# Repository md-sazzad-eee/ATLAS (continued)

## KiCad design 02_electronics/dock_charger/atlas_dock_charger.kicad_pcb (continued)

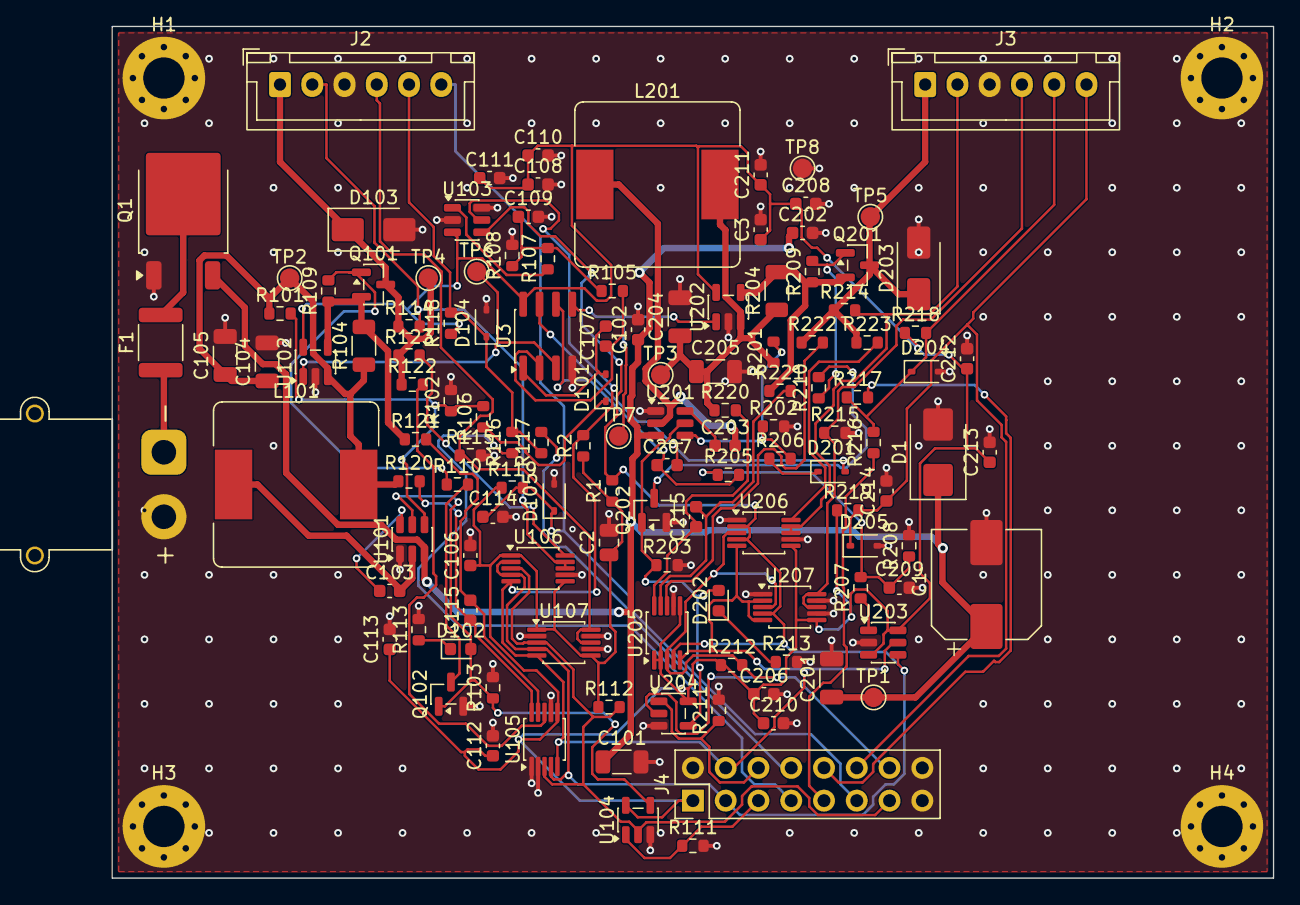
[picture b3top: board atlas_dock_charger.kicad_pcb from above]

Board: 2 copper layers, 90.0 x 66.0 mm, 131 parts (0 on the bottom side), 63 nets.

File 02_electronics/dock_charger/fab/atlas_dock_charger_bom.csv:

"Refs","Value","Footprint","Qty","DNP"
"C1","100uF 25V","Capacitor_SMD:CP_Elec_8x10","1",""
"C2","10uF","Capacitor_SMD:C_0805_2012Metric","1",""
"C3","100nF","Capacitor_SMD:C_0603_1608Metric","1",""
"C101","10uF 25V","Capacitor_SMD:C_1206_3216Metric","1",""
"C102","100nF","Capacitor_SMD:C_0603_1608Metric","1",""
"C103","100nF","Capacitor_SMD:C_0603_1608Metric","1",""
"C104","22uF 25V","Capacitor_SMD:C_1206_3216Metric","1",""
"C105","22uF 25V","Capacitor_SMD:C_1206_3216Metric","1",""
"C106","100nF","Capacitor_SMD:C_0603_1608Metric","1",""
"C107","100nF","Capacitor_SMD:C_0603_1608Metric","1",""
"C108","100nF","Capacitor_SMD:C_0603_1608Metric","1",""
"C109","1uF","Capacitor_SMD:C_0603_1608Metric","1",""
"C110","100nF","Capacitor_SMD:C_0603_1608Metric","1",""
"C111","100nF","Capacitor_SMD:C_0603_1608Metric","1",""
"C112","100nF","Capacitor_SMD:C_0603_1608Metric","1",""
"C113","100nF","Capacitor_SMD:C_0603_1608Metric","1",""
"C114","100nF","Capacitor_SMD:C_0603_1608Metric","1",""
"C115","100nF","Capacitor_SMD:C_0603_1608Metric","1",""
"C201","10uF 25V","Capacitor_SMD:C_1206_3216Metric","1",""
"C202","100nF","Capacitor_SMD:C_0603_1608Metric","1",""
"C203","100nF","Capacitor_SMD:C_0603_1608Metric","1",""
"C204","22uF 25V","Capacitor_SMD:C_1206_3216Metric","1",""
"C205","22uF 25V","Capacitor_SMD:C_1206_3216Metric","1",""
"C206","100nF","Capacitor_SMD:C_0603_1608Metric","1",""
"C207","100nF","Capacitor_SMD:C_0603_1608Metric","1",""
"C208","100nF","Capacitor_SMD:C_0603_1608Metric","1",""
"C209","1uF","Capacitor_SMD:C_0603_1608Metric","1",""
"C210","100nF","Capacitor_SMD:C_0603_1608Metric","1",""
"C211","100nF","Capacitor_SMD:C_0603_1608Metric","1",""
"C212","100nF","Capacitor_SMD:C_0603_1608Metric","1",""
"C213","100nF","Capacitor_SMD:C_0603_1608Metric","1",""
"C214","100nF","Capacitor_SMD:C_0603_1608Metric","1",""
"C215","100nF","Capacitor_SMD:C_0603_1608Metric","1",""
"D1","SMBJ16CA","Diode_SMD:D_SMB","1",""
"D101","BAT54J","Diode_SMD:D_SOD-323","1",""
"D102","AMBER charging","LED_SMD:LED_0603_1608Metric","1",""
"D103","SMAJ12CA","Diode_SMD:D_SMA","1",""
"D104","PESD5V0S1BL","Diode_SMD:D_SOD-323","1",""
"D105","PESD5V0S1BL","Diode_SMD:D_SOD-323","1",""
"D201","BAT54J","Diode_SMD:D_SOD-323","1",""
"D202","AMBER charging","LED_SMD:LED_0603_1608Metric","1",""
"D203","SMAJ12CA","Diode_SMD:D_SMA","1",""
"D204","PESD5V0S1BL","Diode_SMD:D_SOD-323","1",""
"D205","PESD5V0S1BL","Diode_SMD:D_SOD-323","1",""
"F1","3A hold PTC","Fuse:Fuse_1812_4532Metric","1",""
"J1","VIN 4S (+,-)","Connector_AMASS:AMASS_XT30PW-M_1x02_P2.50mm_Horizontal","1",""
"J2","BAY 1 DOCK (VF,VS,GF,GS,DATA,ID)","Connector_JST:JST_XH_B6B-XH-A_1x06_P2.50mm_Vertical","1",""
"J3","BAY 2 DOCK (VF,VS,GF,GS,DATA,ID)","Connector_JST:JST_XH_B6B-XH-A_1x06_P2.50mm_Vertical","1",""
"J4","TO BOARD A","Connector_PinHeader_2.54mm:PinHeader_2x08_P2.54mm_Vertical","1",""
"L101","22uH 2.5A","Inductor_SMD:L_Bourns_SRR1260","1",""
"L201","22uH 2.5A","Inductor_SMD:L_Bourns_SRR1260","1",""
"Q1","AOD409 (rev-pol)","Package_TO_SOT_SMD:TO-252-2","1",""
"Q101","AO3401A","Package_TO_SOT_SMD:SOT-23","1",""
"Q102","2N7002","Package_TO_SOT_SMD:SOT-23","1",""
"Q201","AO3401A","Package_TO_SOT_SMD:SOT-23","1",""
"Q202","2N7002","Package_TO_SOT_SMD:SOT-23","1",""
"R1","2.2k","Resistor_SMD:R_0603_1608Metric","1",""
"R2","2.2k","Resistor_SMD:R_0603_1608Metric","1",""
"R101","130k 0.1%","Resistor_SMD:R_0603_1608Metric","1",""
"R102","10.0k 0.1%","Resistor_SMD:R_0603_1608Metric","1",""
"R103","100k","Resistor_SMD:R_0603_1608Metric","1",""
"R104","20m 1%","Resistor_SMD:R_1206_3216Metric","1",""
"R105","10k","Resistor_SMD:R_0603_1608Metric","1",""
"R106","10k","Resistor_SMD:R_0603_1608Metric","1",""
"R107","10k","Resistor_SMD:R_0603_1608Metric","1",""
"R108","10k","Resistor_SMD:R_0603_1608Metric","1",""
"R109","100k","Resistor_SMD:R_0603_1608Metric","1",""
"R110","10k","Resistor_SMD:R_0603_1608Metric","1",""
"R111","100k","Resistor_SMD:R_0603_1608Metric","1",""
"R112","10k","Resistor_SMD:R_0603_1608Metric","1",""
"R113","1k","Resistor_SMD:R_0603_1608Metric","1",""
"R114","100k","Resistor_SMD:R_0603_1608Metric","1",""
"R115","100k","Resistor_SMD:R_0603_1608Metric","1",""
"R116","1k","Resistor_SMD:R_0603_1608Metric","1",""
"R117","1k","Resistor_SMD:R_0603_1608Metric","1",""
"R118","10k","Resistor_SMD:R_0603_1608Metric","1",""
"R119","10k","Resistor_SMD:R_0603_1608Metric","1",""
"R120","10R","Resistor_SMD:R_0603_1608Metric","1",""
"R121","10R","Resistor_SMD:R_0603_1608Metric","1",""
"R122","10R","Resistor_SMD:R_0603_1608Metric","1",""
"R123","10R","Resistor_SMD:R_0603_1608Metric","1",""
"R201","130k 0.1%","Resistor_SMD:R_0603_1608Metric","1",""
"R202","10.0k 0.1%","Resistor_SMD:R_0603_1608Metric","1",""
"R203","100k","Resistor_SMD:R_0603_1608Metric","1",""
"R204","20m 1%","Resistor_SMD:R_1206_3216Metric","1",""
"R205","10k","Resistor_SMD:R_0603_1608Metric","1",""
"R206","10k","Resistor_SMD:R_0603_1608Metric","1",""
"R207","10k","Resistor_SMD:R_0603_1608Metric","1",""
"R208","10k","Resistor_SMD:R_0603_1608Metric","1",""
"R209","100k","Resistor_SMD:R_0603_1608Metric","1",""
"R210","10k","Resistor_SMD:R_0603_1608Metric","1",""
"R211","100k","Resistor_SMD:R_0603_1608Metric","1",""
"R212","10k","Resistor_SMD:R_0603_1608Metric","1",""
"R213","1k","Resistor_SMD:R_0603_1608Metric","1",""
"R214","100k","Resistor_SMD:R_0603_1608Metric","1",""
"R215","100k","Resistor_SMD:R_0603_1608Metric","1",""
"R216","1k","Resistor_SMD:R_0603_1608Metric","1",""
"R217","1k","Resistor_SMD:R_0603_1608Metric","1",""
"R218","10k","Resistor_SMD:R_0603_1608Metric","1",""
"R219","10k","Resistor_SMD:R_0603_1608Metric","1",""
"R220","10R","Resistor_SMD:R_0603_1608Metric","1",""
"R221","10R","Resistor_SMD:R_0603_1608Metric","1",""
"R222","10R","Resistor_SMD:R_0603_1608Metric","1",""
"R223","10R","Resistor_SMD:R_0603_1608Metric","1",""
"U3","LMV358","Package_SO:SOIC-8_3.9x4.9mm_P1.27mm","1",""
"U101","TPS54202DDC","Package_TO_SOT_SMD:SOT-23-6","1",""
"U102","INA180A2","Package_TO_SOT_SMD:SOT-23-5","1",""
"U103","MCP4725A0T-E/CH","Package_TO_SOT_SMD:SOT-23-6","1",""
"U104","74LVC1G08","Package_TO_SOT_SMD:SOT-23-5","1",""
"U105","INA226 (I, V)","Package_SO:MSOP-10_3x3mm_P0.5mm","1",""
"U106","INA226 (VCHG contact)","Package_SO:MSOP-10_3x3mm_P0.5mm","1",""
"U107","INA226 (GND contact)","Package_SO:MSOP-10_3x3mm_P0.5mm","1",""
"U201","TPS54202DDC","Package_TO_SOT_SMD:SOT-23-6","1",""
"U202","INA180A2","Package_TO_SOT_SMD:SOT-23-5","1",""
"U203","MCP4725A0T-E/CH","Package_TO_SOT_SMD:SOT-23-6","1",""
"U204","74LVC1G08","Package_TO_SOT_SMD:SOT-23-5","1",""
"U205","INA226 (I, V)","Package_SO:MSOP-10_3x3mm_P0.5mm","1",""
"U206","INA226 (VCHG contact)","Package_SO:MSOP-10_3x3mm_P0.5mm","1",""
"U207","INA226 (GND contact)","Package_SO:MSOP-10_3x3mm_P0.5mm","1",""

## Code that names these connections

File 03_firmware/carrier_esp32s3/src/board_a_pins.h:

/* Board A rev A pin map. Source of truth: 02_electronics/carrier_controller/design/board_a_design.py */
#pragma once
#define PIN_VBAT_SENSE  1    /* ADC1_CH0, 100k/18k */
#define PIN_IMOT_LF     2    /* ADC1_CH1, INA180A1 x20 on 20 mOhm: 0.4 V per A */
#define PIN_ID_1        3    /* ADC1_CH2, Board C: 10k pull-up, agent 10k/22k */
#define PIN_IMOT_LR     4
#define PIN_IMOT_RF     5
#define PIN_IMOT_RR     6
#define PIN_ID_2        7
#define PIN_I2C_SDA     8
#define PIN_I2C_SCL     9
#define PIN_MOT_L_IN1  10    /* both left DRV8871s */
#define PIN_MOT_L_IN2  11
#define PIN_MOT_R_IN1  12    /* both right DRV8871s */
#define PIN_MOT_R_IN2  13
#define PIN_ENC_LF_A   14
#define PIN_ENC_LF_B   15
#define PIN_ENC_LR_A   16
#define PIN_ENC_LR_B   17
#define PIN_ENC_RF_A   18
#define PIN_ENC_RF_B   21
#define PIN_ENC_RR_A   35
#define PIN_ENC_RR_B   36
#define PIN_MOT_EN     37    /* AND-ed with WDT_OK, ESTOP_OK, BAY_SAFE_1/2 in hardware */
#define PIN_WDI        38
#define PIN_DATA_TX_1  39
#define PIN_DATA_RX_1  40
#define PIN_DATA_TX_2  41
#define PIN_DATA_RX_2  42
#define PIN_ESTOP_OK   43
#define PIN_EXP_INT    44
#define PIN_LATCH_1    45    /* strap: low at reset == latch locked */
#define PIN_LATCH_2    46
#define PIN_BAY_EN_1   47
#define PIN_BAY_EN_2   48
#define I2C_TCA9534    0x20
#define I2C_DAC_1      0x60
#define I2C_DAC_2      0x61
/* INA226 per bay: { shunt (I, Vpad), VCHG contact, GND contact } */
#define INA_BAY1       {0x40, 0x46, 0x44}
#define INA_BAY2       {0x45, 0x42, 0x43}

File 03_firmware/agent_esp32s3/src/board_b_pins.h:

/* Board B rev A1 pin map. Source of truth: 02_electronics/agent_controller/design/board_b_design.py
 * (verified against the KiCad netlist by verify_netlist.py). Do not edit one without the other. */
#pragma once
#define PIN_I2C_SDA      1
#define PIN_I2C_SCL      2
#define PIN_PI_RX        3      /* ESP32 RX  <- Pi TX  (UART1) */
#define PIN_VBAT_SENSE   4      /* ADC1_CH3, 100k/22k divider  */
#define PIN_IMOT_L       5      /* ADC1_CH4, INA180A2 x50 on 20 mOhm: 1.0 V per A */
#define PIN_IMOT_R       6      /* ADC1_CH5 */
#define PIN_BATT_NTC     7      /* ADC1_CH6, 10k pull-up to 3V3, 10k NTC (B 3950) to GND */
#define PIN_DOCK_VSENSE  8      /* ADC1_CH7, 100k/22k divider on VCHG */
#define PIN_SENS_ADC     9      /* ADC1_CH8, research instrument analogue output */
#define PIN_SENS_GPIO   10
#define PIN_ENC_L_A     11
#define PIN_ENC_L_B     12
#define PIN_ENC_R_A     13
#define PIN_ENC_R_B     14
#define PIN_MOT_L_IN1   15
#define PIN_MOT_L_IN2   16
#define PIN_LED_STAT    17
#define PIN_PI_PWR_EN   18
#define PIN_MOT_EN      21      /* AND-ed with WDT_OK in hardware (74LVC1G08) */
#define PIN_WDI         38      /* TPS3823 watchdog input, 1.6 s timeout */
#define PIN_DOCK_TX     39      /* UART2, half-duplex DATA pad through 1k */
#define PIN_DOCK_RX     40
#define PIN_CHG_EN      41
#define PIN_MOT_R_IN2   42
#define PIN_MOT_R_IN1   47
#define PIN_PI_TX       48      /* ESP32 TX  -> Pi RX  (UART1) */

#define ADC_CH_VBAT      ADC_CHANNEL_3
#define ADC_CH_IMOT_L    ADC_CHANNEL_4
#define ADC_CH_IMOT_R    ADC_CHANNEL_5
#define ADC_CH_NTC       ADC_CHANNEL_6
#define ADC_CH_DOCK      ADC_CHANNEL_7
#define ADC_CH_SENS      ADC_CHANNEL_8

#define DIV_VBAT_NUM 122        /* (100k + 22k) / 22k */
#define DIV_VBAT_DEN 22

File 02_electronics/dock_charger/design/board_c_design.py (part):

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  Pad switch  AO3401A high-side, off unless EN_n = BAY_EN_n (Board A, only in DOCKED) AND
              KALERT_N_n (Kelvin over-resistance trip) -> buck EN driven by the same signal.
  Telemetry   INA226 #1 on the shunt (I, V at the pad); INA226 #2 / #3 measure the drop across the
              VCHG and GND contacts by 4-wire (Kelvin) sensing: each agent pad is touched by a force pin
              and a separate sense pin, so V_force - V_sense = I * R_contact exactly.
              COMSOL/MATLAB: > ~100 mOhm overheats the contact block -> INA226 ALERT trips EN in hardware.
  Data / ID   half-duplex UART on DATA (1k series, 10k pull-up, ESD), ID pull-up 10k -> ADC on Board A
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    cap(f"C{k+6}", "100nF", 140, y0 + 25, "VCC_3V3", "GND")
    # --- CC integrator (LMV358 unit n) + FB injection
    ua = n                                       # unit 1 for bay 1, unit 2 for bay 2
    pins = {1: dict(_1=f"CCOUT_1", _2="CCINV_1", _3="ISNS_1"), 2: dict(_7="CCOUT_2", _6="CCINV_2", _5="ISNS_2")}[n]
    if n == 1:
        part("U3", "Amplifier_Operational:LMV358", "LMV358", "Package_SO:SOIC-8_3.9x4.9mm_P1.27mm", 160, 60 + 150, 0,
             _4="GND", _8="VCC_3V3", _1="CCOUT_1", _2="CCINV_1", _3="ISNS_1",
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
